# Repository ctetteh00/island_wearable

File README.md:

# 🌡️ Heat Risk Monitoring System

A dual-device system for real-time, personalized heat stress monitoring. Combines ESP32-based wearable and stationary nodes with a Firebase-connected dashboard to calculate the Modified Physiological Strain Index (mPSI), Heat Index, and a user-specific risk score.

## 🚀 Project Structure

- **Stationary Device**: Measures ambient temperature and humidity, broadcasts data via ESP-NOW.
- **Wearable Device**: Receives strongest signal, calculates skin temperature, uploads all data to Firebase.
- **Web Dashboard**: Real-time interface for monitoring risk levels and metrics.

---

## Repository Structure
/island_wearable/
├── firmware/
│   ├── wearable.ino         # Wearable ESP32 firmware
│   ├── stationary.ino       # Stationary ESP32 firmware
│   └── secrets.h            # Credentials (use from .env)
├── public/
│   ├── index.html           # Web UI
│   ├── app.js               # Logic & Firebase JS SDK
├── docs/
│   ├── 462_island_wearable_2.zip
    ├── wearable.kicad_pcb
    ├── wearable.kicad_pro
    ├── wearable.kicad_sch 
    ├── wearable_circuit_schematic.png
    ├── wearable_pcb_schematic.png
│   └── stationary_schematic.png
├── .env                     # Environment variables
├── setup_dependencies.sh # Library Dependencies for Arduino
├── README.md

## 📦 Hardware Components

### Wearable Device

| Component           | Part Number            | Description                          |
|--------------------|------------------------|--------------------------------------|
| Microcontroller     | Arduino Nano ESP32     | Wi-Fi + ESP-NOW                      |
| Temperature Sensor  | TMP236                 | Skin temperature measurement         |
| Charging Module     | Adafruit PowerBoost 1000C | LiPo charging circuit             |
| Battery             | LP103454               | 3.7V 1000mAh LiPo                    |
| Strap & Enclosure   | Chest band + PLA case  | Wearability and housing              |

### Stationary Device

| Component           | Part Number            | Description                          |
|--------------------|------------------------|--------------------------------------|
| Microcontroller     | Arduino Nano ESP32     | ESP-NOW broadcaster                  |
| Sensor              | DHT22                  | Temp + Humidity measurement          |
| Power               | 9V Battery + Switch    | Portable outdoor deployment          |
| Case                | Acrylic Enclosure      | Ventilated weather housing           |

---

## 🧠 Features

- ESP-NOW peer-to-peer communication
- RSSI-based device proximity selection
- mPSI calculation with exponential calibration
- Firebase-hosted real-time database
- Personalized scoring with comorbidities, sleep, and medications
- Dynamic UI with recommendations and color-coded feedback

---

## 🌐 Firebase Setup Instructions

1. **Create a Firebase Project**
   - Go to [Firebase Console](https://console.firebase.google.com/)
   - Click **Add Project** → Give it a name → Continue
   - Disable Google Analytics (optional)

2. **Add Realtime Database**
   - Navigate to `Build > Realtime Database`
   - Create a new database in test mode (can secure later)

3. **Set Up Web App**
   - Click **</>** to register a new Web App in Firebase
   - Save the API Key and Database URL (add to `.env`)

4. **Enable Authentication (Optional)**
   - Go to `Authentication > Sign-in method`
   - Enable "Email/Password" or other methods

---

## 🔒 Environment Configuration

Add a `.env` file in the root of your repo:

```env
# Firebase Credentials
FIREBASE_API_KEY=your_api_key_here
FIREBASE_DATABASE_URL=https://your-database-name.firebaseio.com

# WiFi Access
WIFI_SSID="YourNetwork"
WIFI_PASSWORD="YourPassword"

# Optional
WIFI_CHANNEL=1

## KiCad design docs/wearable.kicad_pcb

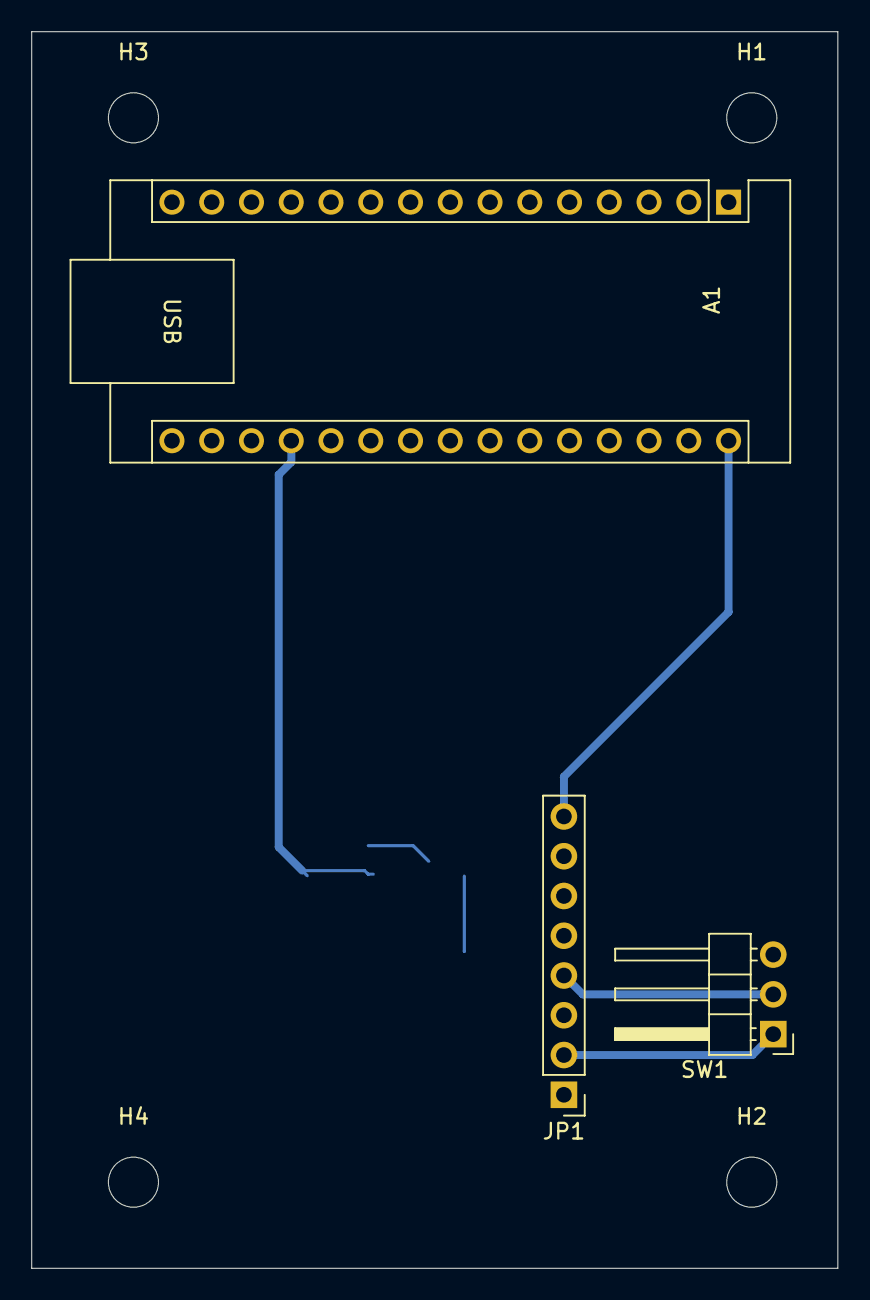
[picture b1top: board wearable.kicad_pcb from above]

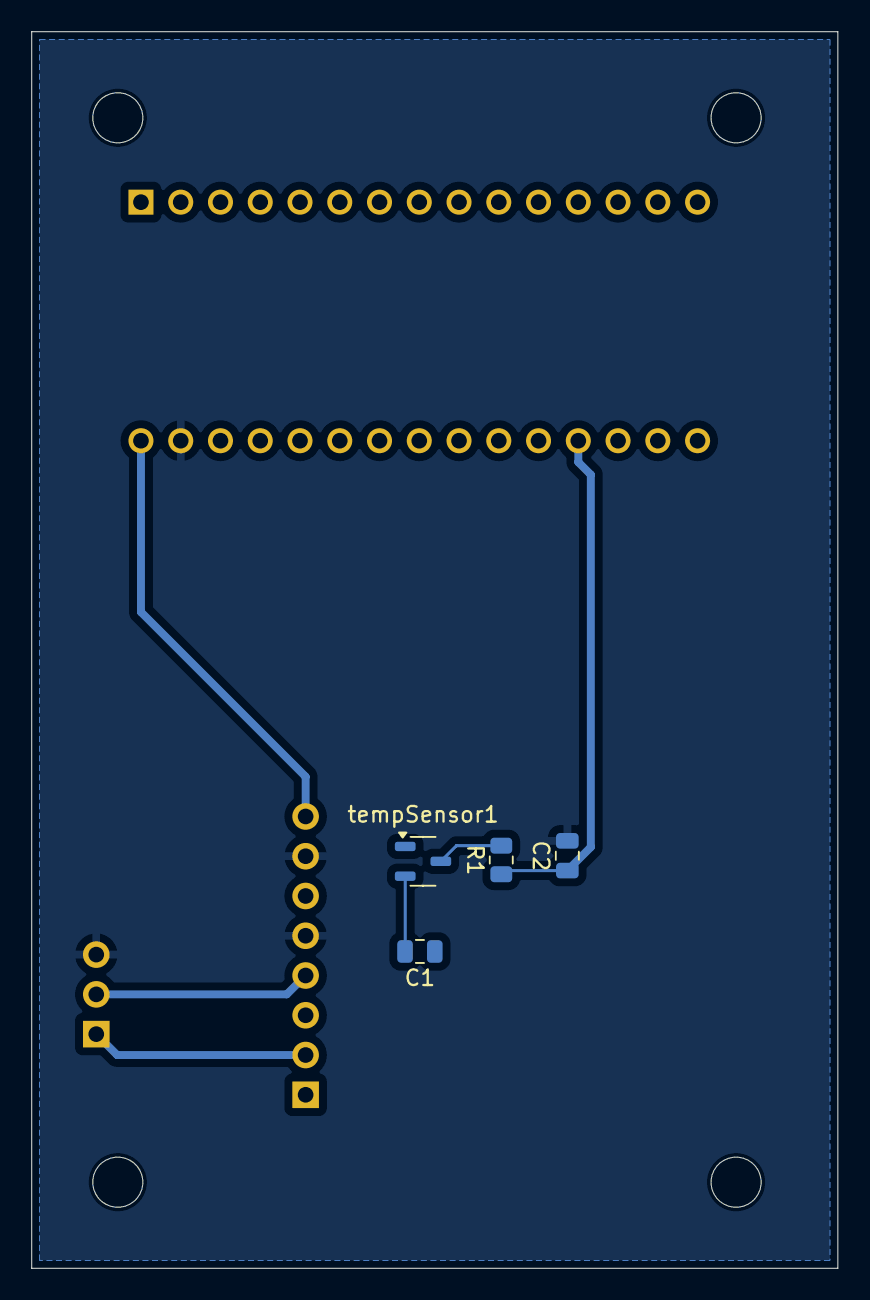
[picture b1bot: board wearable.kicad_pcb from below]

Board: 2 copper layers, 51.5 x 79.0 mm, 11 parts (4 on the bottom side), 7 nets.

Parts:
A1: Arduino_Nano_v2.x; Arduino_Nano
C1, C2: C_Small; C_0805_2012Metric
H1, H2, H3, H4: MountingHole; MountingHole_3.2mm_M3
JP1: HEADER-1X8ROUND; PinHeader_1x08_P2.54mm_Vertical
R1: R_Small; R_0805_2012Metric
SW1: SW_DPDT_x2; PinHeader_1x03_P2.54mm_Horizontal
tempSensor1: TMP20AIDRL; SOT-23-3

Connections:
5.0V: A1.30 (VIN), JP1.8
/ENABLE: JP1.4, SW1.2 (B)
GND: A1.29 (GND), C2.2, JP1.5, JP1.7, SW1.3 (C)
unnamed: A1.19 (A0), C2.1, R1.1
unnamed: C1.2, tempSensor1.2 (GND)
unnamed: R1.2, tempSensor1.3 (V_{OUT})
VLIPO: JP1.2, SW1.1 (A)

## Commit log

2025-04-19 adding files to the repository
2025-04-19 equation modifications:
2025-04-22 arduino files
2025-04-22 pushing all files up
